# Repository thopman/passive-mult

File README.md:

# passive-mult

Simple multiple configured for 1x7 operation. 

By changing the jumper configuration it can be configured as a normalised 1x6 multiple, that turns into 2 independent
1x3 multiples when a cable is inserted into J5.

Short jumper SJ1 and leave SJ2 open for 1x7 operation.

Short jumper SJ2 and leave SJ1 open for 1x6/2x3 operation.

<------------------------------------------------------------------------------------------------------------------------------>

By Thomas Hopman/TomaTek 2017

This work is licensed under a [Creative Commons Attribution-ShareAlike 4.0 International License](http://creativecommons.org/licenses/by-sa/4.0/)

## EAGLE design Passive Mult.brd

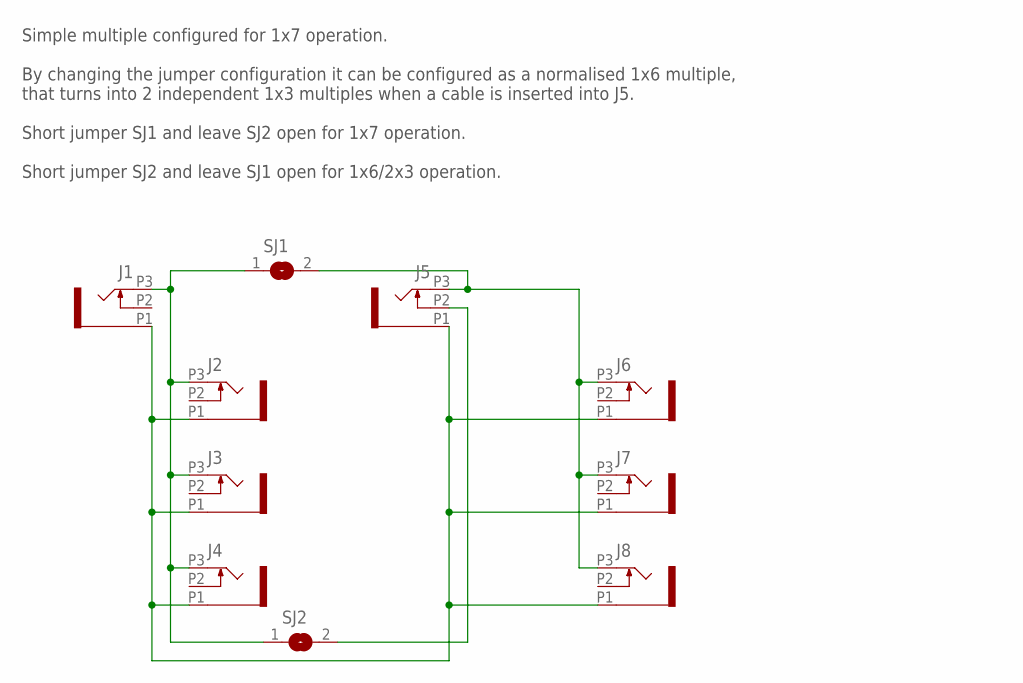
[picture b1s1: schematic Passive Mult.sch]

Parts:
J1, J2, J3, J4, J5, J6, J7, J8: OG-PJ301_PJ301_THONKICONN4; OG-PJ301_WQP_PJ_301M4
SJ1, SJ2: SJ

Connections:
GND: J1.P1 (1), J2.P1 (1), J3.P1 (1), J4.P1 (1), J5.P1 (1), J6.P1 (1), J7.P1 (1), J8.P1 (1)
unnamed: J5.P2 (2), SJ2.2
unnamed: J1.P3 (3), J2.P3 (3), J3.P3 (3), J4.P3 (3), SJ1.1, SJ2.1
unnamed: J5.P3 (3), J6.P3 (3), J7.P3 (3), J8.P3 (3), SJ1.2

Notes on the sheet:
Simple multiple configured for 1x7 operation. By changing the jumper configuration it can be configured as a normalised 1x6 multiple, that turns into 2 independent 1x3 multiples when a cable is inserted into J5. Short jumper SJ1 and leave SJ2 open for 1x7 operation. Short jumper SJ2 and leave SJ1 o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

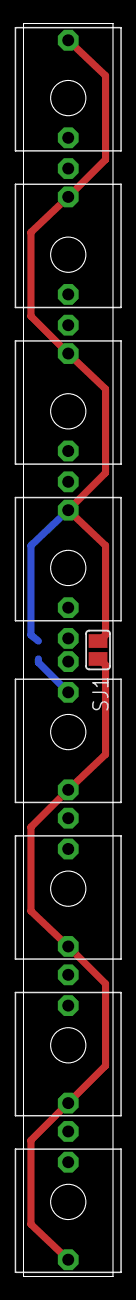
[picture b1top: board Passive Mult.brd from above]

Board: 2 copper layers, 7.6 x 106.7 mm, 11 parts (1 on the bottom side), 4 nets.

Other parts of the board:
U$1: OG-EURORACK-TEMPLATE_EURORACK_TEMPLATE

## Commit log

2017-02-06 update Readme.md
    update readme
2017-02-06 BottomSilk updated, front-panel holes and dimension dxf added

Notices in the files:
README.md:
CC BY-SA 4.0
